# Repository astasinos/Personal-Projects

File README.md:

# Personal-Projects
This repository contains most of my personal projects

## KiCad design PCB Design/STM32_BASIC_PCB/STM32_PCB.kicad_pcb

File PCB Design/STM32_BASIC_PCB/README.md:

This repository contains the first attempt to design an STM32 Based PCB. The PCB features a UART and I2C connection and is powered through USB with a 3.3V Voltage Regulator. 
The Microcontroller can be programmed via SWD and also a BOOT selection switch was added.

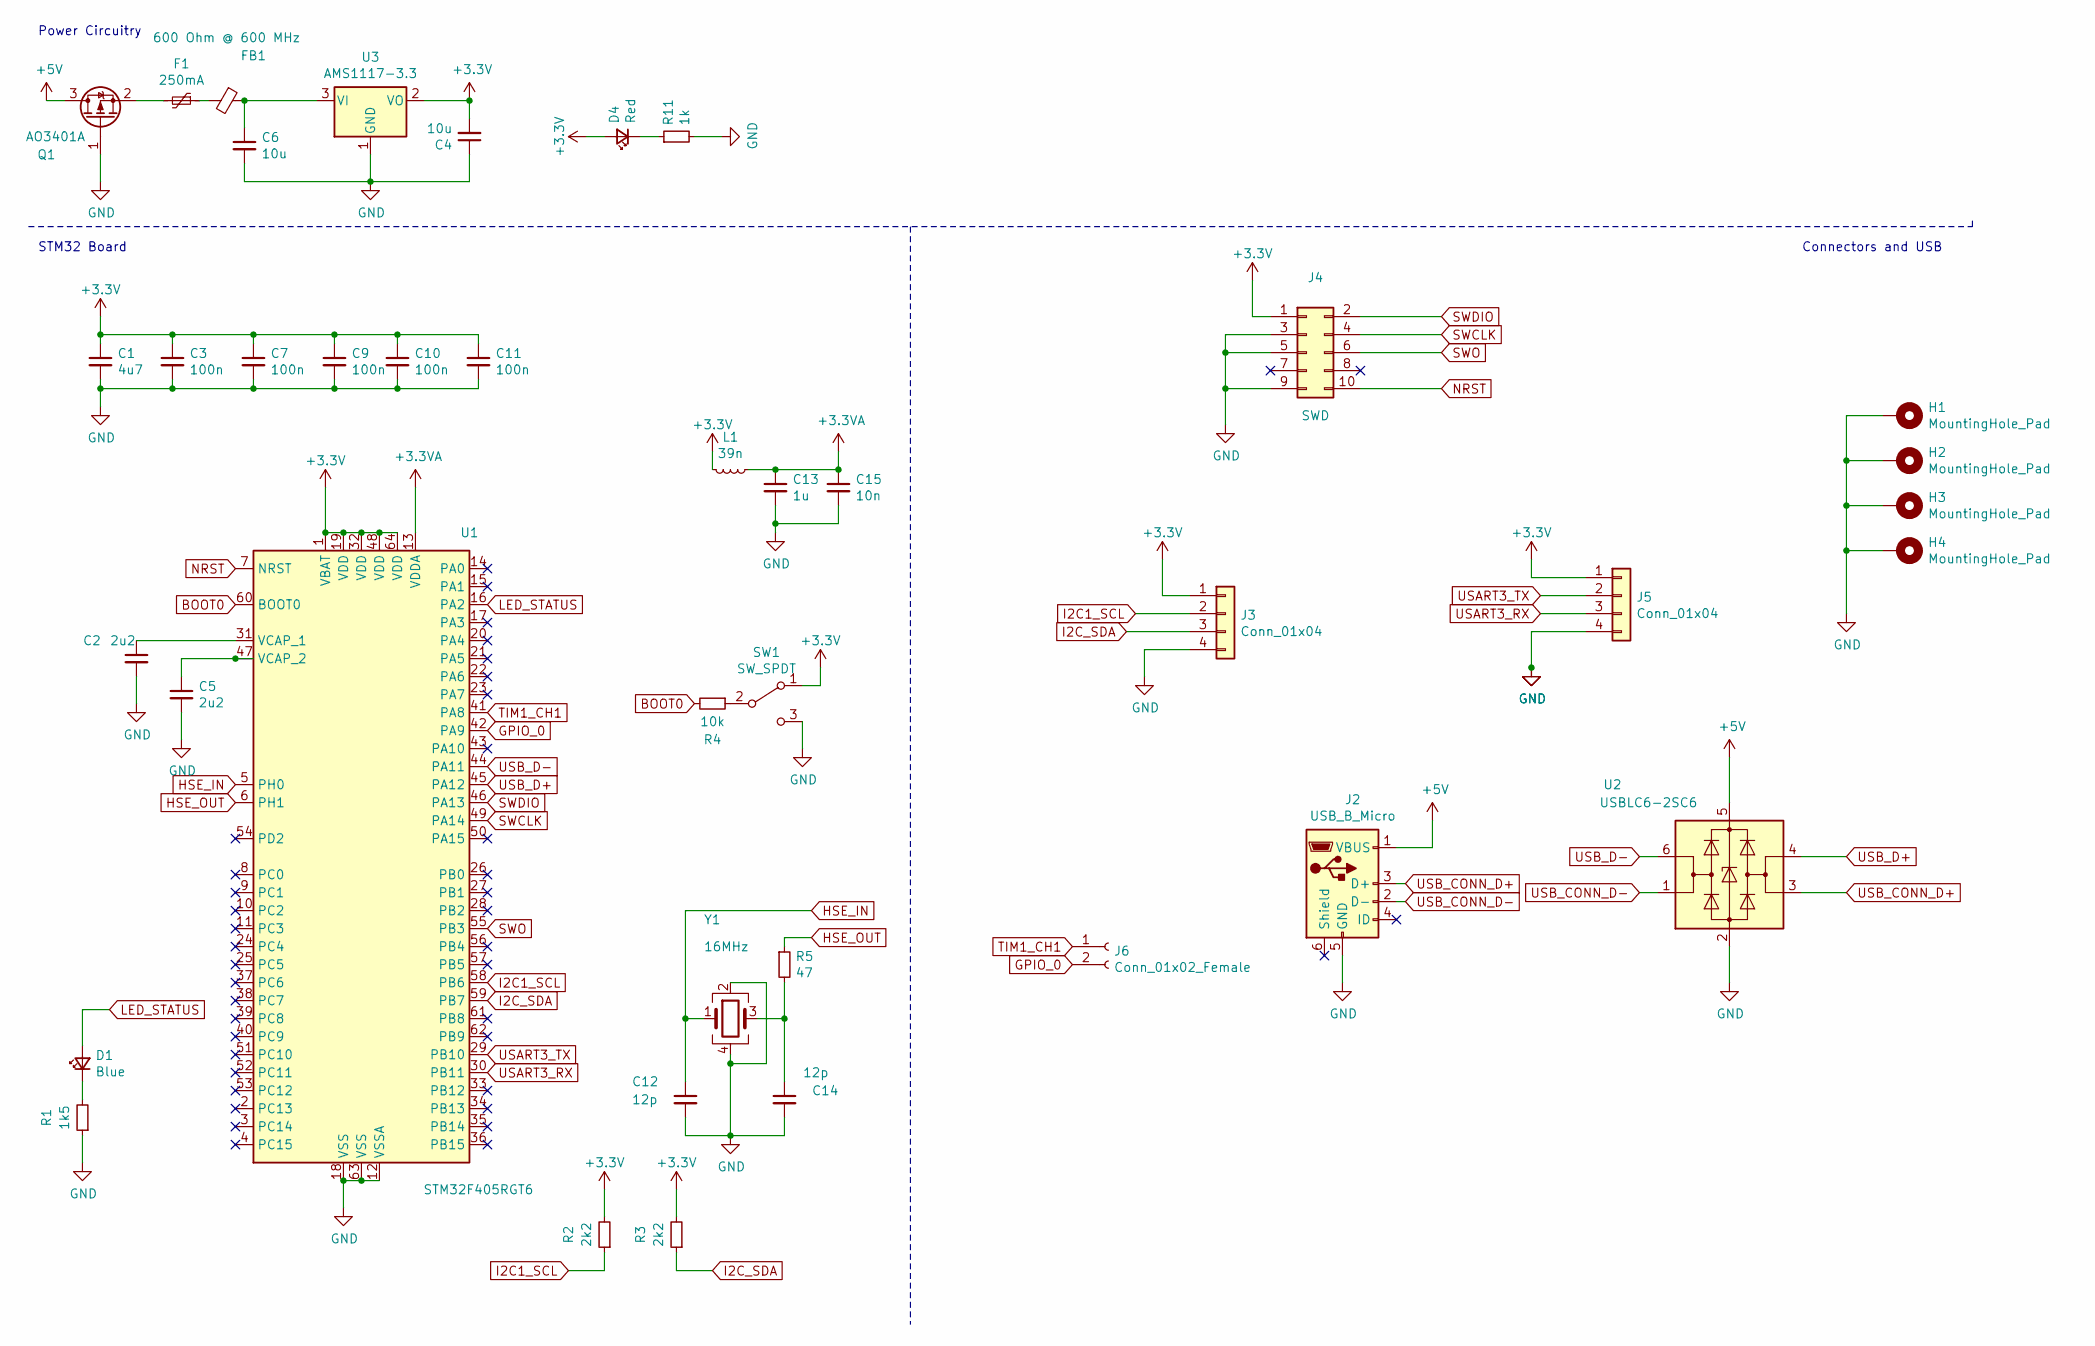
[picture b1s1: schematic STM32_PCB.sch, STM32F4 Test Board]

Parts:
C1: 4u7; C_0603_1608Metric; LCSC Part # C19666
C2, C5: 2u2; C_0603_1608Metric; LCSC Part # C23630
C3, C7, C9, C10, C11: 100n; C_0402_1005Metric; LCSC Part # C1525
C4, C6: 10u; C_1206_3216Metric; LCSC Part # C13585
C12, C14: 12p; C_0402_1005Metric; LCSC Part # C1547
C13: 1u; C_0402_1005Metric; LCSC Part # C52923
C15: 10n; C_0603_1608Metric; LCSC Part # C1589
D1: Blue; LED_0603_1608Metric; LCSC Part # C72041
D4: Red; LED_0603_1608Metric; LCSC Part # C2286
F1: 250mA; Fuse_1206_3216Metric; LCSC Part # C369159
FB1: 600 Ohm @ 600 MHz; L_0805_2012Metric; LCSC Part # C1017
H1, H2, H3, H4: MountingHole_Pad; MountingHole_4.3mm_M4_Pad_Via
J2: USB_B_Micro; USB_Micro-B_Molex-105017-0001; LCSC Part # C404969
J3, J5: Conn_01x04; Molex_PicoBlade_53048-0410_1x04_P1.25mm_Horizontal; LCSC Part # C22843
J4: SWD; PinHeader_2x05_P1.27mm_Vertical_SMD; LCSC Part # C239059
J6: Conn_01x02_Female; PinSocket_1x02_P2.54mm_Vertical; LCSC Part # C541849
L1: 39n; L_0402_1005Metric; LCSC Part # C26443
Q1: AO3401A; SOT-23; LCSC Part # C15127
R1: 1k5; R_0603_1608Metric; LCSC Part # C22843
R2, R3: 2k2; R_0603_1608Metric; LCSC Part # C4190
R4: 10k; R_0402_1005Metric; LCSC Part # C25744
R5: 47; R_0402_1005Metric; LCSC Part # C25118
R11: 1k; R_0603_1608Metric; LCSC Part # C21190
SW1: SW_SPDT; SW_SPDT_PCM12; LCSC Part # C405951
U1: STM32F405RGT6; LQFP-64_10x10mm_P0.5mm; LCSC Part # C15742
U2: USBLC6-2SC6; SOT-23-6; LCSC Part # C7519
U3: AMS1117-3.3; SOT-223-3_TabPin2; LCSC Part # C6186
Y1: 16MHz; Crystal_SMD_3225-4Pin_3.2x2.5mm; LCSC Part # C13738

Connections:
+3.3VA: C13.1, C15.1, L1.1, U1.13 (VDDA)
+3V3: C1.1, C3.1, C4.2, C7.1, C9.1, C10.1, C11.1, D4.2 (A), J3.1, J4.1, J5.1, L1.2, R2.2, R3.2, SW1.1 (A), U1.1 (VBAT), U1.19 (VDD), U1.32 (VDD), U1.48 (VDD), U1.64 (VDD), U3.2 (VO)
+5V: J2.1 (VBUS), Q1.3 (D), U2.5 (VBUS)
BOOT0: R4.2, U1.60 (BOOT0)
GND: C1.2, C2.2, C3.2, C4.1, C5.2, C6.2, C7.2, C9.2, C10.2, C11.2, C12.2, C13.2, C14.2, C15.2, H1.1, H2.1, H3.1, H4.1, J2.5 (GND), J3.4, J4.3, J4.5, J4.9, J5.4, Q1.1 (G), R1.1, R11.2, SW1.3 (C), U1.12 (VSSA), U1.18 (VSS), U1.63 (VSS), U2.2 (GND), U3.1 (GND), Y1.2, Y1.4
GPIO_0: J6.2, U1.42 (PA9)
HSE_IN: C12.1, U1.5 (PH0), Y1.1
HSE_OUT: R5.1, U1.6 (PH1)
I2C1_SCL: J3.2, R2.1, U1.58 (PB6)
I2C_SDA: J3.3, R3.1, U1.59 (PB7)
LED_STATUS: D1.2 (A), U1.16 (PA2)
NRST: J4.10, U1.7 (NRST)
unnamed: C2.1, U1.31 (VCAP_1)
unnamed: C5.1, U1.47 (VCAP_2)
unnamed: C6.1, FB1.1, U3.3 (VI)
unnamed: C14.1, R5.2, Y1.3
unnamed: D1.1 (K), R1.2
unnamed: D4.1 (K), R11.1
unnamed: F1.1, FB1.2
unnamed: F1.2, Q1.2 (S)
unnamed: R4.1, SW1.2 (B)
SWCLK: J4.4, U1.49 (PA14)
SWDIO: J4.2, U1.46 (PA13)
SWO: J4.6, U1.55 (PB3)
TIM1_CH1: J6.1, U1.41 (PA8)
USART3_RX: J5.3, U1.30 (PB11)
USART3_TX: J5.2, U1.29 (PB10)
USB_CONN_D+: J2.3 (D+), U2.3 (I/O2)
USB_CONN_D-: J2.2 (D-), U2.1 (I/O1)
USB_D+: U1.45 (PA12), U2.4 (I/O2)
USB_D-: U1.44 (PA11), U2.6 (I/O1)

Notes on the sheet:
STM32 Board
Power Circuitry
Connectors and USB

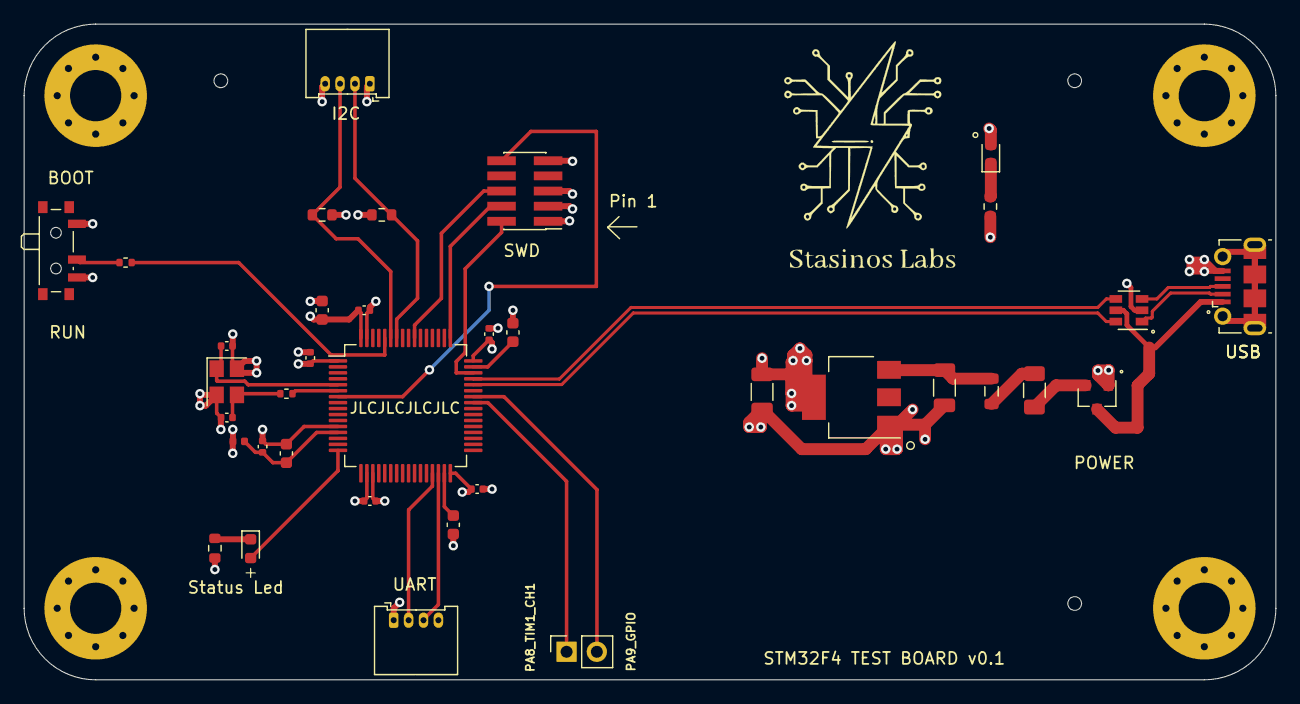
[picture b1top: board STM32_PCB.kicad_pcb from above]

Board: 4 copper layers, 105.0 x 55.0 mm, 40 parts (0 on the bottom side), 31 nets.

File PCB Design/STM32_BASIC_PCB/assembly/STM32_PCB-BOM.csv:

Comment,Designator,Footprint,LCSC, LCSC Part #
"4u7","C1","Capacitor_SMD:C_0603_1608Metric","","C19666"
"100n","C11,C10,C9,C7,C3","Capacitor_SMD:C_0402_1005Metric","","C1525"
"1u","C13","Capacitor_SMD:C_0402_1005Metric","","C52923"
"12p","C14,C12","Capacitor_SMD:C_0402_1005Metric","","C1547"
"10n","C15","Capacitor_SMD:C_0603_1608Metric","","C1589"
"2u2","C2,C5","Capacitor_SMD:C_0603_1608Metric","","C23630"
"10u","C6,C4","Capacitor_SMD:C_1206_3216Metric","","C13585"
"Blue","D1","LED_SMD:LED_0603_1608Metric","","C72041"
"Red","D4","LED_SMD:LED_0603_1608Metric","","C2286"
"250mA","F1","Fuse:Fuse_1206_3216Metric","","C369159"
"600 Ohm @ 600 MHz","FB1","Inductor_SMD:L_0805_2012Metric","","C1017"
"MountingHole_Pad","H1,H2,H3,H4","MountingHole:MountingHole_4.3mm_M4_Pad_Via",""
"USB_B_Micro","J2","Connector_USB:USB_Micro-B_Molex-105017-0001","","C404969"
"Conn_01x04","J3,J5","Connector_Molex:Molex_PicoBlade_53048-0410_1x04_P1.25mm_Horizontal","","C22843"
"SWD","J4","Connector_PinHeader_1.27mm:PinHeader_2x05_P1.27mm_Vertical_SMD",""," C239059"
"Conn_01x02_Female","J6","Connector_PinSocket_2.54mm:PinSocket_1x02_P2.54mm_Vertical","","C541849"
"39n","L1","Inductor_SMD:L_0402_1005Metric","","C26443"
"AO3401A","Q1","Package_TO_SOT_SMD:SOT-23","","C15127"
"1k5","R1","Resistor_SMD:R_0603_1608Metric","","C22843"
"1k","R11","Resistor_SMD:R_0603_1608Metric","","C21190"
"2k2","R2,R3","Resistor_SMD:R_0603_1608Metric","","C4190"
"10k","R4","Resistor_SMD:R_0402_1005Metric","","C25744"
"47","R5","Resistor_SMD:R_0402_1005Metric","","C25118"
"SW_SPDT","SW1","Button_Switch_SMD:SW_SPDT_PCM12","","C405951"
"STM32F405RGT6","U1","Package_QFP:LQFP-64_10x10mm_P0.5mm","","C15742"
"USBLC6-2SC6","U2","Package_TO_SOT_SMD:SOT-23-6","","C7519"
"AMS1117-3.3","U3","Package_TO_SOT_SMD:SOT-223-3_TabPin2","","C6186"
"16MHz","Y1","Crystal:Crystal_SMD_3225-4Pin_3.2x2.5mm","","C13738"

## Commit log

2021-05-01 Organize in folders
2021-05-01 Add Buck Converter project
2021-05-11 Fix Polygon Pour Error
